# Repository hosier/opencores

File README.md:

opencores
=========

RCOS OpenCores Contribution

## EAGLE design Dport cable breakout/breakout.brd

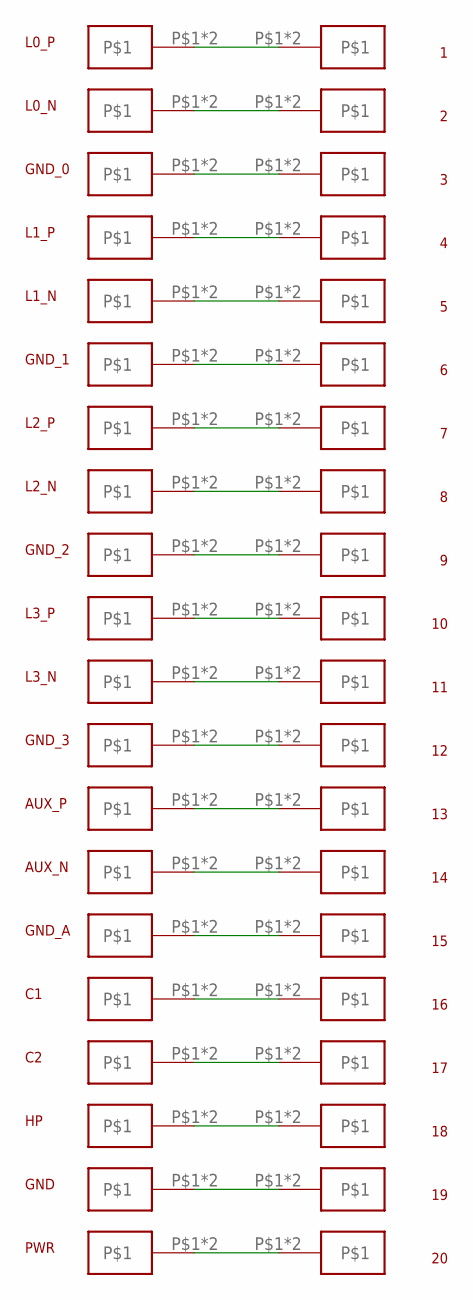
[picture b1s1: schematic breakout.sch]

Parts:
1, 2, 3, 4, 5, 6, 7, 8, 9, 10, 11, 12, 13, 14, 15, 16, 17, 18, 19, 20: 30_AWG_PAD
AUX_N: 30_AWG_PAD
AUX_P: 30_AWG_PAD
C1, C2: 30_AWG_PAD
GND: 30_AWG_PAD
GND_0, GND_1, GND_2, GND_3: 30_AWG_PAD
GND_A: 30_AWG_PAD
HP: 30_AWG_PAD
L0_N, L0_P, L1_N, L1_P, L2_N, L2_P, L3_N, L3_P: 30_AWG_PAD
PWR: 30_AWG_PAD

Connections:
unnamed: 1.P$1, 1.P$2, L0_P.P$1, L0_P.P$2
unnamed: 2.P$1, 2.P$2, L0_N.P$1, L0_N.P$2
unnamed: 3.P$1, 3.P$2, GND_0.P$1, GND_0.P$2
unnamed: 4.P$1, 4.P$2, L1_P.P$1, L1_P.P$2
unnamed: 5.P$1, 5.P$2, L1_N.P$1, L1_N.P$2
unnamed: 6.P$1, 6.P$2, GND_1.P$1, GND_1.P$2
unnamed: 7.P$1, 7.P$2, L2_P.P$1, L2_P.P$2
unnamed: 8.P$1, 8.P$2, L2_N.P$1, L2_N.P$2
unnamed: 9.P$1, 9.P$2, GND_2.P$1, GND_2.P$2
unnamed: 10.P$1, 10.P$2, L3_P.P$1, L3_P.P$2
unnamed: 11.P$1, 11.P$2, L3_N.P$1, L3_N.P$2
unnamed: 12.P$1, 12.P$2, GND_3.P$1, GND_3.P$2
unnamed: 13.P$1, 13.P$2, AUX_P.P$1, AUX_P.P$2
unnamed: 14.P$1, 14.P$2, AUX_N.P$1, AUX_N.P$2
unnamed: 15.P$1, 15.P$2, GND_A.P$1, GND_A.P$2
unnamed: 16.P$1, 16.P$2, C1.P$1, C1.P$2
unnamed: 17.P$1, 17.P$2, C2.P$1, C2.P$2
unnamed: 18.P$1, 18.P$2, HP.P$1, HP.P$2
unnamed: 19.P$1, 19.P$2, GND.P$1, GND.P$2
unnamed: 20.P$1, 20.P$2, PWR.P$1, PWR.P$2

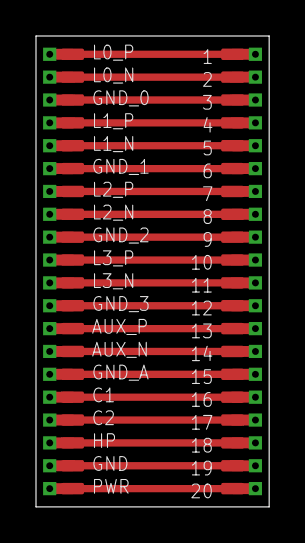
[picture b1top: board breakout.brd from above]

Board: 2 copper layers, 13.0 x 26.2 mm, 40 parts (0 on the bottom side), 20 nets.

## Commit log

2014-05-27 Create gh-pages branch via GitHub
2014-06-06 Displayport documentation added
    Will be using the old specification, 1.1, instead of 1.2, because I
    don't have free access to the new one
2014-06-06 test
    test
2014-06-17 added 8b/10b library
    displayport data is 8b/10b encoded
2014-07-01 more notes and documentation, also a simple breakout board pcb
2014-07-15 some more reading/documentation
2014-07-19 manchester encoding library
    manchester encoding is used for aux ch
2014-07-21 DPCD and EDID information updated
    spreadsheet describing contents of DisplayPort Configuration Data and
    Extended Display Identification Data
